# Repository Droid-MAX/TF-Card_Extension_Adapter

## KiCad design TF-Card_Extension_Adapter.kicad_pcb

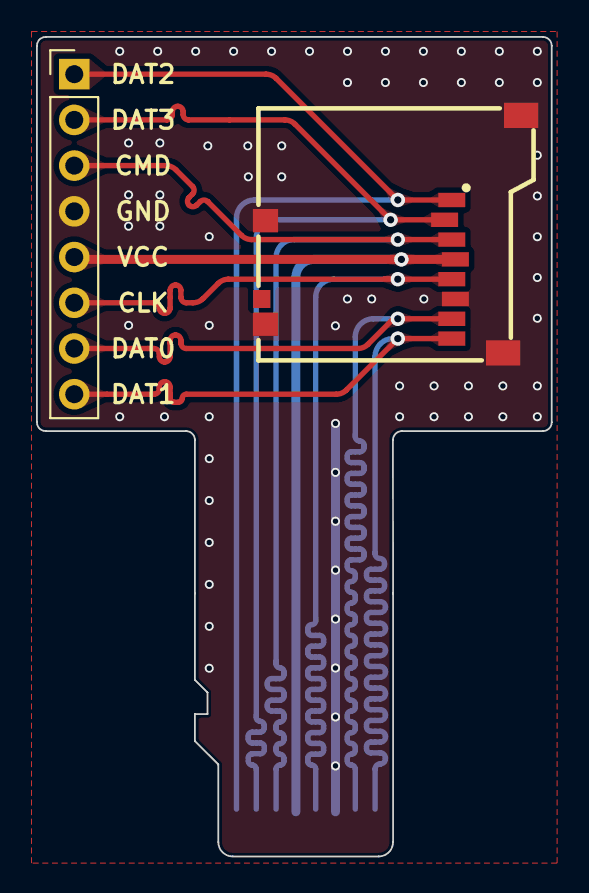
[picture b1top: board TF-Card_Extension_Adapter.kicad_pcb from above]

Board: 2 copper layers, 28.6 x 45.5 mm, 3 parts (1 on the bottom side), 8 nets.

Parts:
J1: Conn_01x08_Pin; PinHeader_1x08_P2.54mm_Vertical
J2: TF_Card_Slot; TF-SMD_TF-101A-P3
J3: TF_Card; TFCARD

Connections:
GND: J1.4, J2.6 (VSS), J2.9 (SHELL), J2.10 (SHELL), J2.11 (SHELL), J2.12 (SHELL), J3.6 (VSS)
unnamed: J1.1, J2.1 (DAT2), J3.1 (DAT2)
unnamed: J1.2, J2.2 (CD/DAT3), J3.2 (DAT3)
unnamed: J1.3, J2.3 (CMD), J3.3 (CMD)
unnamed: J1.6, J2.5 (CLK), J3.5 (CLK)
unnamed: J1.7, J2.7 (DAT0), J3.7 (DAT0)
unnamed: J1.8, J2.8 (DAT1), J3.8 (DAT1)
VCC: J1.5, J2.4 (VDD), J3.4 (VDD)

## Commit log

2023-08-28 first release
2023-08-29 feat: Adjust SDIO wiring to equal length
2023-09-08 feat: Adjust the sdio signal line width to 0.3mm
